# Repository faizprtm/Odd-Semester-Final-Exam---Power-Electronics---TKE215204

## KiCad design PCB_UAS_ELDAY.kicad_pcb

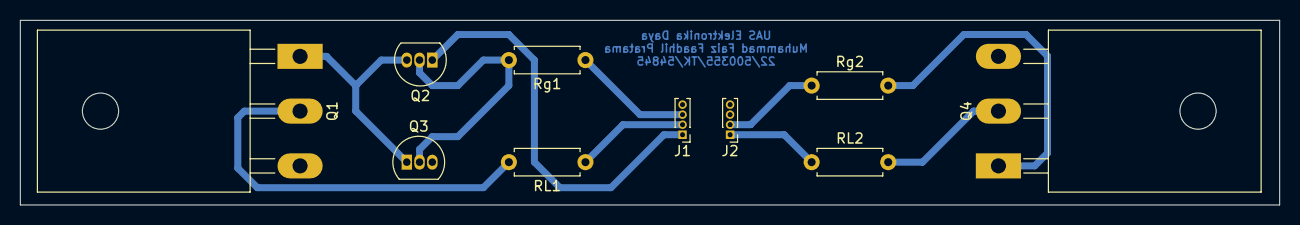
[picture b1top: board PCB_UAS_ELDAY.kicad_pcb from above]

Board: 2 copper layers, 125.3 x 18.4 mm, 10 parts (0 on the bottom side), 11 nets.

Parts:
J1, J2: Conn_01x04_Pin; PinHeader_1x04_P1.00mm_Vertical
Q1, Q4: NMOS; TO-247-3_Horizontal_TabUp
Q2: NPN; TO-92L_Inline
Q3: PNP; TO-92L_Inline
RL1, RL2: 100; R_Axial_DIN0207_L6.3mm_D2.5mm_P7.62mm_Horizontal
Rg1, Rg2: 100; R_Axial_DIN0207_L6.3mm_D2.5mm_P7.62mm_Horizontal

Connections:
GND: J1.4, J2.3, J2.4, Q1.3 (S), Q3.3 (E), Q4.3 (S)
unnamed: Q1.2 (G), RL1.2
unnamed: Q1.1 (D), Q2.3 (E), Q3.1 (C)
unnamed: Q2.2 (B), Q3.2 (B), Rg1.2
unnamed: Q4.2 (G), RL2.2
unnamed: Q4.1 (D), Rg2.2
PWM1: J2.2, Rg2.1
PWM2: J1.3, Rg1.1
Vd1: J1.1, Q2.1 (C)
Vd2: J2.1, RL2.1
Vs: J1.2, RL1.1

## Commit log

2025-12-22 PCB_UAS_ELDAY 2025
    desain rangkaian pcb eksperimen low-side and totem-pole gate driver
2025-12-22 FAB_FILE_PCB_ELDAY2025
    File untuk manuf/fabrikasi pcb fix project UAS ELDAY
2025-12-22 Simulasi Task 1
    Low side gate driver - Totem pole gate driver
    Simulasi menggunakan LTspices
2025-12-24 Data FFT Half Bridge
2025-12-24 Half Bridge LC Filter Second Order
2025-12-24 Laporan Tugas UAS Elektronika Daya
2025-12-24 Data Eksperimen UAS Elday
